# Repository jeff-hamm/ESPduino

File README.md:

# espduino
A platform that assists in making writing and deploying code for the ESP8266 as easy as writing arduino code.

#External Dependencies
Eagle 7.2
Python27
SimpleParse 2.1
GerbV http://sourceforge.net/projects/gerbv/files/gerbv/gerbv-2.6.0/gerbvinst-2.6.0.exe

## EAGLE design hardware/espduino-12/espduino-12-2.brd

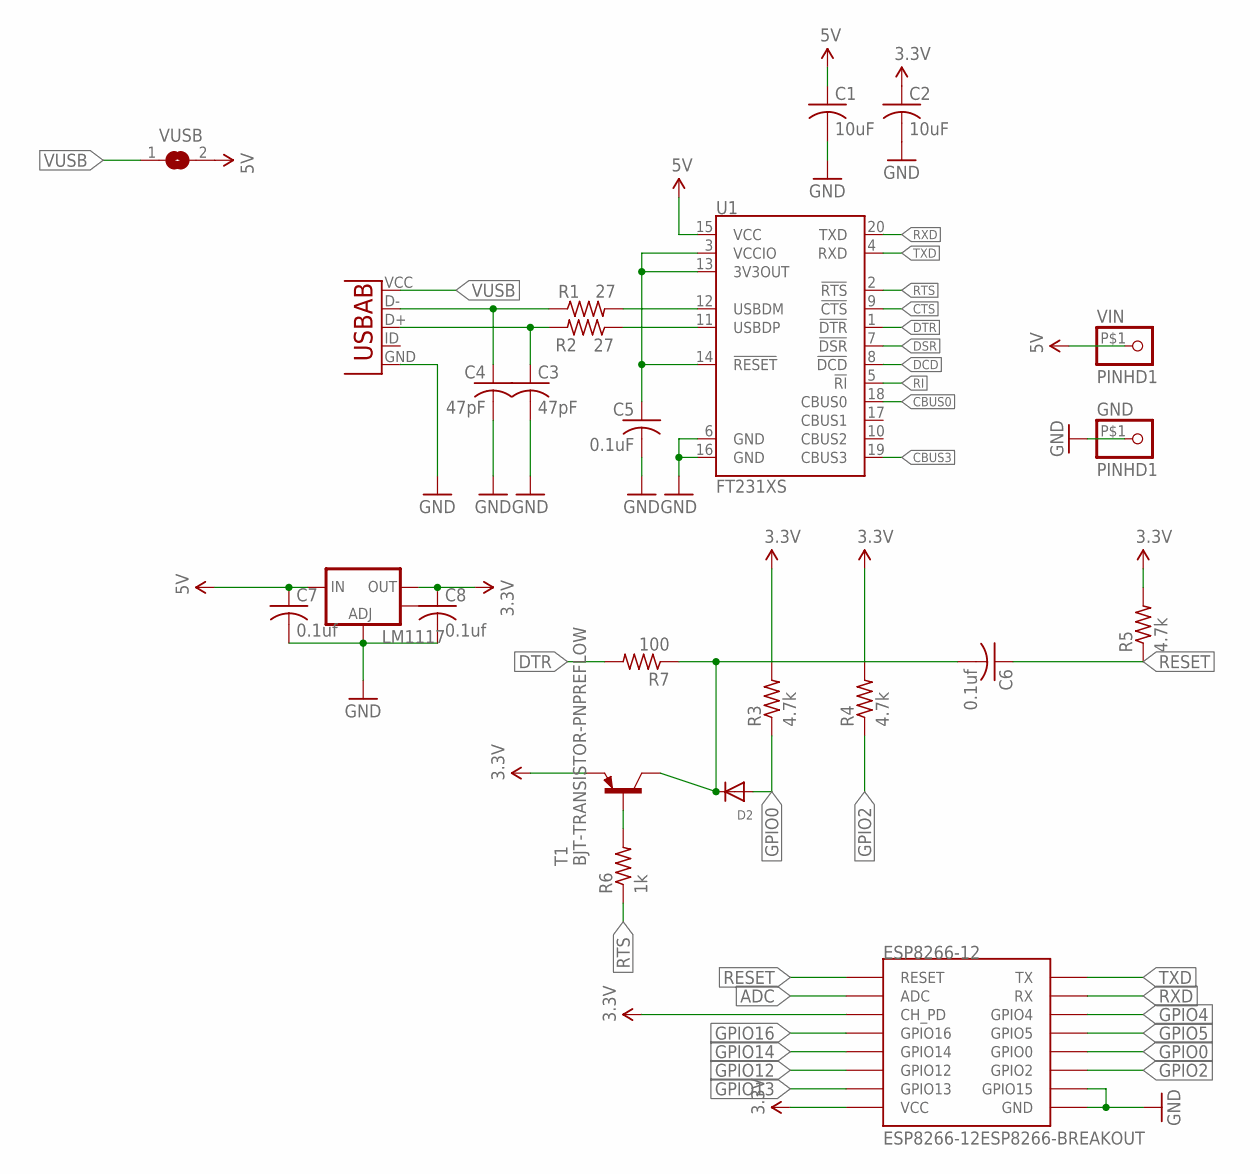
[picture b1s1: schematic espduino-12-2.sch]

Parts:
C1, C2: 10uF; C0603
C3, C4: 47pF; C0603
C5: 0.1uF; C0603
C6, C7, C8: 0.1uf; C0603
D2: DIODESOT23_REFLOW; SOT23-R
ESP8266-12: ESP8266-12ESP8266-BREAKOUT; ESP8266-12-EXT-HEADERS
GND: PINHD1
LM1117: V_REG_LM1117SOT223; SOT223
R1, R2: 27; R0603
R3, R4, R5: 4.7k; R0603
R6: 1k; R0603
R7: 100; R0603
T1: BJT-TRANSISTOR-PNPREFLOW; SOT23-R
U1: FT231XS; SSOP20_L
U2: USB-AB; MICRO-USB-A01SB141B1
VIN: PINHD1
VUSB: SJCUTTABLE; SJ-CUTTABLE

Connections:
3.3V: C2.1, C8.1, ESP8266-12.CH_PD, ESP8266-12.VCC, ESP8266-12.VCC_P (VCC), LM1117.2 (OUT), R3.2, R4.2, R5.2, T1.2 (E)
5V: C1.1, C7.1, LM1117.3 (IN), U1.15 (VCC), VIN.P$1, VUSB.2
ADC: ESP8266-12.ADC, ESP8266-12.ADC_P (ADC)
CBUS0: U1.18 (CBUS0)
CBUS3: U1.19 (CBUS3)
CTS: U1.9 (!CTS)
DCD: U1.8 (!DCD)
DSR: U1.7 (!DSR)
DTR: R7.2, U1.1 (!DTR)
GND: C1.2, C2.2, C3.2, C4.2, C5.2, C7.2, C8.2, ESP8266-12.GND, ESP8266-12.GND_P (GND), ESP8266-12.GPIO15, GND.P$1, LM1117.1 (ADJ), U1.6 (GND), U1.16 (GND), U2.GND
GPIO0: D2.1 (A), ESP8266-12.GPIO0, ESP8266-12.GPIO0_P (GPIO0), R3.1
GPIO2: ESP8266-12.GPIO2, ESP8266-12.GPIO2_P (GPIO2), R4.1
GPIO4: ESP8266-12.GPIO4, ESP8266-12.GPIO4_P (GPIO4)
GPIO5: ESP8266-12.GPIO5, ESP8266-12.GPIO5_P (GPIO5)
GPIO12: ESP8266-12.GPIO12, ESP8266-12.GPIO12_P (GPIO12)
GPIO13: ESP8266-12.GPIO13, ESP8266-12.GPIO13_P (GPIO13)
GPIO14: ESP8266-12.GPIO14, ESP8266-12.GPIO14_P (GPIO14)
GPIO16: ESP8266-12.GPIO16, ESP8266-12.GPIO_16_P (GPIO16)
unnamed: R1.2, U1.12 (USBDM)
unnamed: R2.1, U1.11 (USBDP)
unnamed: C3.1, R2.2, U2.D+
unnamed: C4.1, R1.1, U2.D-
unnamed: C5.1, U1.3 (VCCIO), U1.13 (3V3OUT), U1.14 (!RESET)
unnamed: R6.2, T1.1 (B)
NOT_DTR: C6.2, D2.3 (C), R7.1, T1.3 (C)
RESET: C6.1, ESP8266-12.RESET, ESP8266-12.RST_P (RESET), R5.1
RI: U1.5 (!RI)
RTS: R6.1, U1.2 (!RTS)
RXD: ESP8266-12.RX, ESP8266-12.RX_P (RX), U1.20 (TXD)
TXD: ESP8266-12.TX, ESP8266-12.TX_P (TX), U1.4 (RXD)
VUSB: U2.VCC (VBUS), VUSB.1

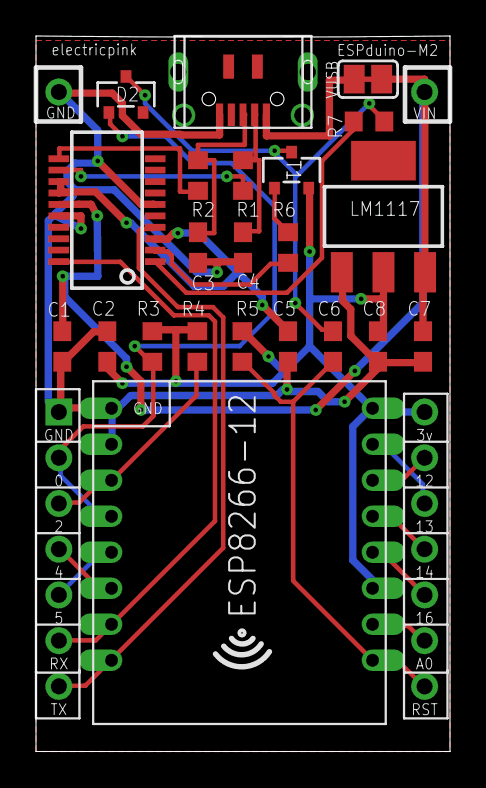
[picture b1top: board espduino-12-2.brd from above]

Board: 2 copper layers, 23.0 x 39.8 mm, 25 parts (0 on the bottom side), 25 nets.

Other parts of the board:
U$2: JUMPER-LOGO-X-SMALL

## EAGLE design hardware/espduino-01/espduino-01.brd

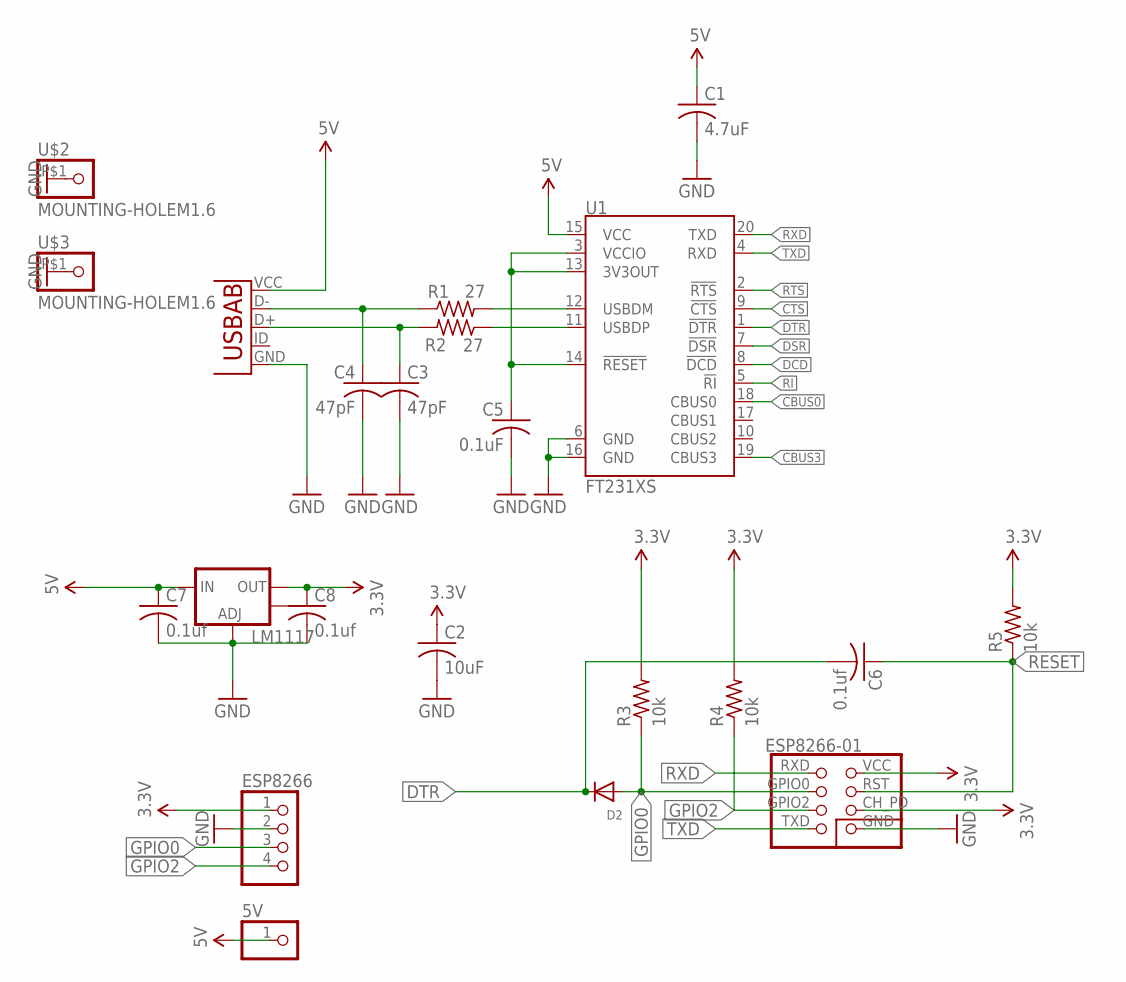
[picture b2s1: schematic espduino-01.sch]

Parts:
5V: PINHD-1X1; 1X01
C1: 4.7uF; C0603
C2: 10uF; C0603
C3, C4: 47pF; C0603
C5: 0.1uF; C0603
C6, C7, C8: 0.1uf; C0603
D2: DIODESOT23_REFLOW; SOT23-R
ESP8266: PINHD-1X4; 1X04
ESP8266-01: ESP8266ESP8266-01-MIN; ESP8266-01-MIN
LM1117: V_REG_LM1117SOT223; SOT223
R1, R2: 27; R0603
R3, R4, R5: 10k; R0603
U1: FT231XS; SSOP20_L
U2: USB-AB; MICRO-USB-A01SB141B1
U$2, U$3: MOUNTING-HOLEM1.6; M1_6MOUNTING_HOLE

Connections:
3.3V: C2.1, C8.1, ESP8266.1, ESP8266-01.CH_PD, ESP8266-01.VCC, LM1117.2 (OUT), R3.2, R4.2, R5.2
5V: 5V.1, C1.1, C7.1, LM1117.3 (IN), U1.15 (VCC), U2.VCC (VBUS)
CBUS0: U1.18 (CBUS0)
CBUS3: U1.19 (CBUS3)
CTS: U1.9 (!CTS)
DCD: U1.8 (!DCD)
DSR: U1.7 (!DSR)
DTR: C6.2, D2.3 (C), U1.1 (!DTR)
GND: C1.2, C2.2, C3.2, C4.2, C5.2, C7.2, C8.2, ESP8266.2, ESP8266-01.GND, LM1117.1 (ADJ), U1.6 (GND), U1.16 (GND), U2.GND, U$2.P$1, U$3.P$1
GPIO0: D2.1 (A), ESP8266.3, ESP8266-01.GPIO0, R3.1
GPIO2: ESP8266.4, ESP8266-01.GPIO2, R4.1
unnamed: R1.2, U1.12 (USBDM)
unnamed: R2.1, U1.11 (USBDP)
unnamed: C3.1, R2.2, U2.D+
unnamed: C4.1, R1.1, U2.D-
unnamed: C5.1, U1.3 (VCCIO), U1.13 (3V3OUT), U1.14 (!RESET)
RESET: C6.1, ESP8266-01.RST, R5.1
RI: U1.5 (!RI)
RTS: U1.2 (!RTS)
RXD: ESP8266-01.RXD, U1.20 (TXD)
TXD: ESP8266-01.TXD, U1.4 (RXD)

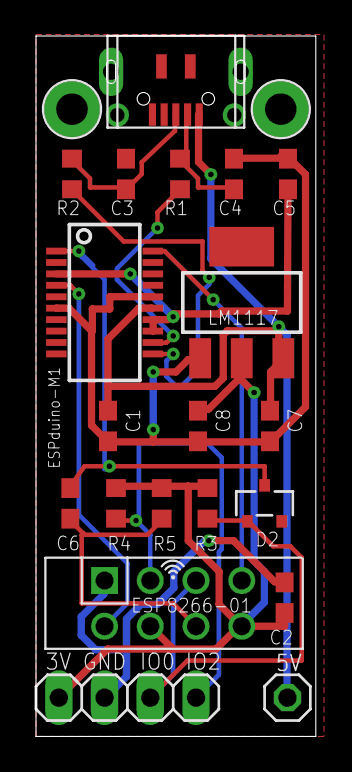
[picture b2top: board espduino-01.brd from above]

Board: 2 copper layers, 15.5 x 38.9 mm, 23 parts (0 on the bottom side), 14 nets.

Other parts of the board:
U$1: JUMPER-LOGO-X-SMALL

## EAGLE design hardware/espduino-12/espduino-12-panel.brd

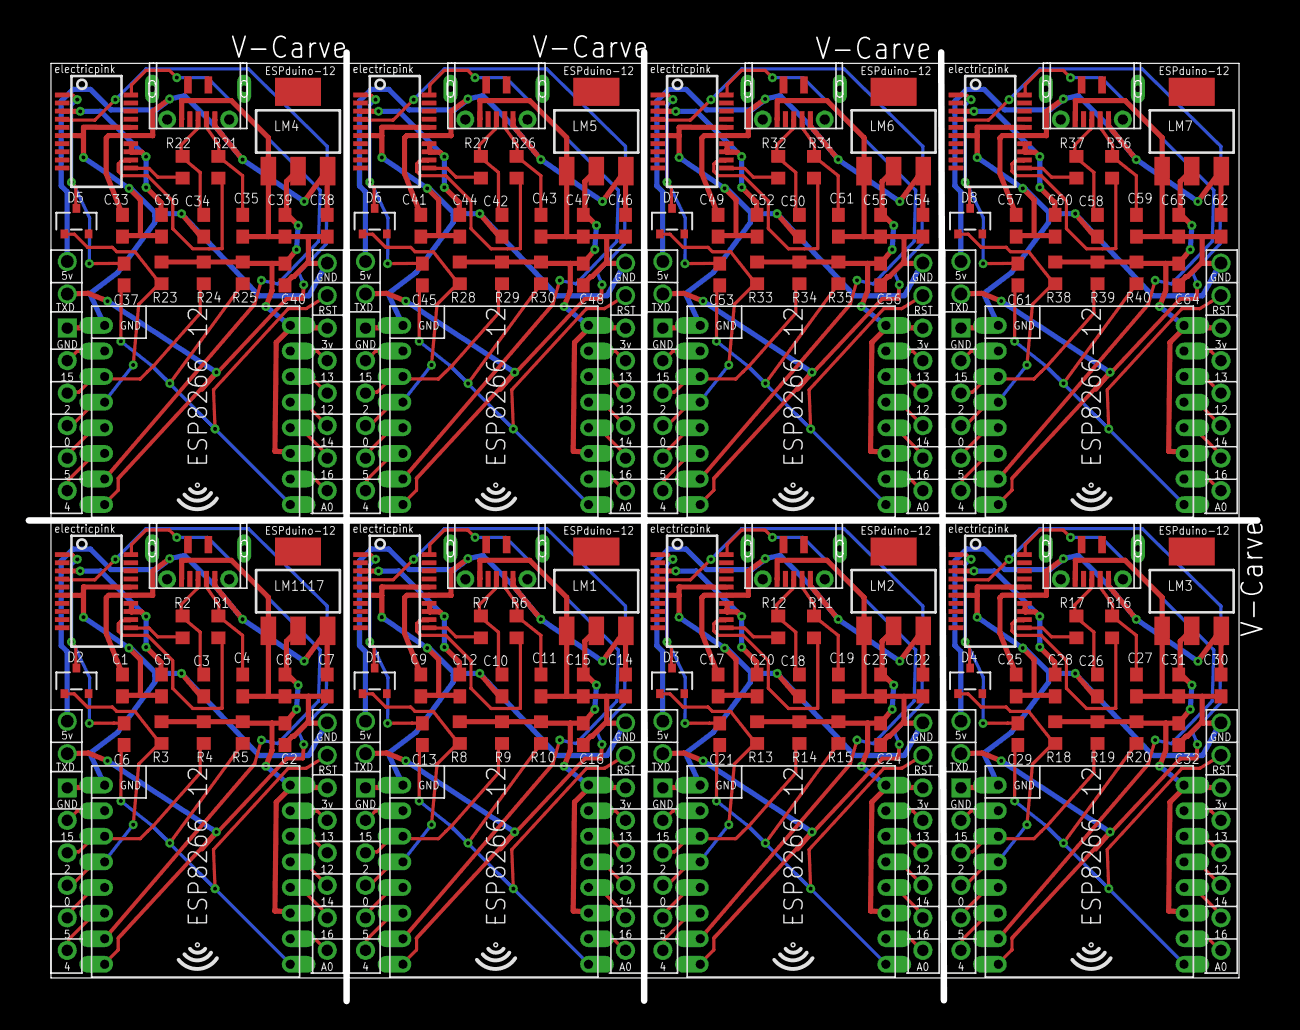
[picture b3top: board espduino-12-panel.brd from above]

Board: 2 copper layers, 97.1 x 76.0 mm, 152 parts (0 on the bottom side), 176 nets.

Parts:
C1, C9, C17, C25, C33, C41, C49, C57: 4.7uF; C0603
C2, C16, C24, C32, C40, C48, C56, C64: 10uF; C0603
C3, C4, C10, C11, C18, C19, C26, C27, C34, C35, C42, C43, C50, C51, C58, C59: 47pF; C0603
C5, C12, C20, C28, C36, C44, C52, C60: 0.1uF; C0603
C6, C7, C8, C13, C14, C15, C21, C22, C23, C29, C30, C31, C37, C38, C39, C45, C46, C47, C53, C54, C55, C61, C62, C63: 0.1uf; C0603
D1, D2, D3, D4, D5, D6, D7, D8: SOT23-R
ESP8266-1, ESP8266-2, ESP8266-3, ESP8266-4, ESP8266-5, ESP8266-6, ESP8266-7, ESP8266-12: ESP8266-12ESP8266-BREAKOUT; ESP8266-12-EXT-HEADERS
LM1, LM2, LM3, LM4, LM5, LM6, LM7, LM1117: SOT223
R1, R2, R6, R7, R11, R12, R16, R17, R21, R22, R26, R27, R31, R32, R36, R37: 27; R0603
R3, R4, R5, R8, R9, R10, R13, R14, R15, R18, R19, R20, R23, R24, R25, R28, R29, R30, R33, R34, R35, R38, R39, R40: 10k; R0603
U1, U3, U5, U7, U9, U11, U13, U15: FT231XS; SSOP20_L
U2, U4, U6, U8, U10, U12, U14, U16: MICRO-USB-A01SB141B1
U$1, U$2, U$3, U$4, U$5, U$6, U$7, U$8: JUMPER-LOGO-X-SMALL

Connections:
3.3V: C2.1, C8.1, ESP8266-12.CH_PD, ESP8266-12.VCC, ESP8266-12.VCC_P, LM1117.2, R3.2, R4.2, R5.2
3.3V1: C15.1, C16.1, ESP8266-1.CH_PD, ESP8266-1.VCC, ESP8266-1.VCC_P, LM1.2, R8.2, R9.2, R10.2
3.3V2: C23.1, C24.1, ESP8266-2.CH_PD, ESP8266-2.VCC, ESP8266-2.VCC_P, LM2.2, R13.2, R14.2, R15.2
3.3V3: C31.1, C32.1, ESP8266-3.CH_PD, ESP8266-3.VCC, ESP8266-3.VCC_P, LM3.2, R18.2, R19.2, R20.2
3.3V4: C39.1, C40.1, ESP8266-4.CH_PD, ESP8266-4.VCC, ESP8266-4.VCC_P, LM4.2, R23.2, R24.2, R25.2
3.3V5: C47.1, C48.1, ESP8266-5.CH_PD, ESP8266-5.VCC, ESP8266-5.VCC_P, LM5.2, R28.2, R29.2, R30.2
3.3V6: C55.1, C56.1, ESP8266-6.CH_PD, ESP8266-6.VCC, ESP8266-6.VCC_P, LM6.2, R33.2, R34.2, R35.2
3.3V7: C63.1, C64.1, ESP8266-7.CH_PD, ESP8266-7.VCC, ESP8266-7.VCC_P, LM7.2, R38.2, R39.2, R40.2
5V: C1.1, C7.1, LM1117.3, U1.15, U2.VCC
5V1: C9.1, C14.1, LM1.3, U3.15, U4.VCC
5V2: C17.1, C22.1, LM2.3, U5.15, U6.VCC
5V3: C25.1, C30.1, LM3.3, U7.15, U8.VCC
5V4: C33.1, C38.1, LM4.3, U9.15, U10.VCC
5V5: C41.1, C46.1, LM5.3, U11.15, U12.VCC
5V6: C49.1, C54.1, LM6.3, U13.15, U14.VCC
5V7: C57.1, C62.1, LM7.3, U15.15, U16.VCC
ADC: ESP8266-12.ADC, ESP8266-12.ADC_P
ADC1: ESP8266-1.ADC, ESP8266-1.ADC_P
ADC2: ESP8266-2.ADC, ESP8266-2.ADC_P
ADC3: ESP8266-3.ADC, ESP8266-3.ADC_P
ADC4: ESP8266-4.ADC, ESP8266-4.ADC_P
ADC5: ESP8266-5.ADC, ESP8266-5.ADC_P
ADC6: ESP8266-6.ADC, ESP8266-6.ADC_P
ADC7: ESP8266-7.ADC, ESP8266-7.ADC_P
DTR: C6.2, D2.3, U1.1
DTR1: C13.2, D1.3, U3.1
DTR2: C21.2, D3.3, U5.1
DTR3: C29.2, D4.3, U7.1
DTR4: C37.2, D5.3, U9.1
DTR5: C45.2, D6.3, U11.1
DTR6: C53.2, D7.3, U13.1
DTR7: C61.2, D8.3, U15.1
GND: C1.2, C2.2, C3.2, C4.2, C5.2, C7.2, C8.2, ESP8266-12.GND, ESP8266-12.GND_P, LM1117.1, U1.6, U1.16, U2.GND
GND1: C9.2, C10.2, C11.2, C12.2, C14.2, C15.2, C16.2, ESP8266-1.GND, ESP8266-1.GND_P, LM1.1, U3.6, U3.16, U4.GND
GND2: C17.2, C18.2, C19.2, C20.2, C22.2, C23.2, C24.2, ESP8266-2.GND, ESP8266-2.GND_P, LM2.1, U5.6, U5.16, U6.GND
GND3: C25.2, C26.2, C27.2, C28.2, C30.2, C31.2, C32.2, ESP8266-3.GND, ESP8266-3.GND_P, LM3.1, U7.6, U7.16, U8.GND
GND4: C33.2, C34.2, C35.2, C36.2, C38.2, C39.2, C40.2, ESP8266-4.GND, ESP8266-4.GND_P, LM4.1, U9.6, U9.16, U10.GND
GND5: C41.2, C42.2, C43.2, C44.2, C46.2, C47.2, C48.2, ESP8266-5.GND, ESP8266-5.GND_P, LM5.1, U11.6, U11.16, U12.GND
GND6: C49.2, C50.2, C51.2, C52.2, C54.2, C55.2, C56.2, ESP8266-6.GND, ESP8266-6.GND_P, LM6.1, U13.6, U13.16, U14.GND
GND7: C57.2, C58.2, C59.2, C60.2, C62.2, C63.2, C64.2, ESP8266-7.GND, ESP8266-7.GND_P, LM7.1, U15.6, U15.16, U16.GND
GPIO0: D2.1, ESP8266-12.GPIO0, ESP8266-12.GPIO0_P, R3.1
GPIO1: D1.1, ESP8266-1.GPIO0, ESP8266-1.GPIO0_P, R8.1
GPIO2: ESP8266-12.GPIO2, ESP8266-12.GPIO2_P, R4.1
GPIO3: ESP8266-1.GPIO2, ESP8266-1.GPIO2_P, R9.1
GPIO4: ESP8266-12.GPIO4, ESP8266-12.GPIO4_P
GPIO5: ESP8266-12.GPIO5, ESP8266-12.GPIO5_P
GPIO6: ESP8266-1.GPIO16, ESP8266-1.GPIO_16_P
GPIO7: ESP8266-1.GPIO14, ESP8266-1.GPIO14_P
GPIO8: ESP8266-1.GPIO12, ESP8266-1.GPIO12_P
GPIO9: ESP8266-1.GPIO13, ESP8266-1.GPIO13_P
GPIO10: ESP8266-1.GPIO4, ESP8266-1.GPIO4_P
GPIO11: ESP8266-1.GPIO5, ESP8266-1.GPIO5_P
GPIO12: ESP8266-12.GPIO12, ESP8266-12.GPIO12_P
GPIO13: ESP8266-12.GPIO13, ESP8266-12.GPIO13_P
GPIO14: ESP8266-12.GPIO14, ESP8266-12.GPIO14_P
GPIO15: ESP8266-12.GPIO15, ESP8266-12.GPIO15_P
GPIO16: ESP8266-12.GPIO16, ESP8266-12.GPIO_16_P
GPIO17: ESP8266-1.GPIO15, ESP8266-1.GPIO15_P
GPIO18: D3.1, ESP8266-2.GPIO0, ESP8266-2.GPIO0_P, R13.1
GPIO19: ESP8266-2.GPIO2, ESP8266-2.GPIO2_P, R14.1
GPIO20: ESP8266-2.GPIO16, ESP8266-2.GPIO_16_P
GPIO21: ESP8266-2.GPIO14, ESP8266-2.GPIO14_P
GPIO22: ESP8266-2.GPIO12, ESP8266-2.GPIO12_P
GPIO23: ESP8266-2.GPIO13, ESP8266-2.GPIO13_P
GPIO24: ESP8266-2.GPIO4, ESP8266-2.GPIO4_P
GPIO25: ESP8266-2.GPIO5, ESP8266-2.GPIO5_P
GPIO26: ESP8266-2.GPIO15, ESP8266-2.GPIO15_P
GPIO27: D4.1, ESP8266-3.GPIO0, ESP8266-3.GPIO0_P, R18.1
GPIO28: ESP8266-3.GPIO2, ESP8266-3.GPIO2_P, R19.1
GPIO29: ESP8266-3.GPIO16, ESP8266-3.GPIO_16_P
GPIO30: ESP8266-3.GPIO14, ESP8266-3.GPIO14_P
GPIO31: ESP8266-3.GPIO12, ESP8266-3.GPIO12_P
GPIO32: ESP8266-3.GPIO13, ESP8266-3.GPIO13_P
GPIO33: ESP8266-3.GPIO4, ESP8266-3.GPIO4_P
GPIO34: ESP8266-3.GPIO5, ESP8266-3.GPIO5_P
GPIO35: ESP8266-3.GPIO15, ESP8266-3.GPIO15_P
GPIO36: D5.1, ESP8266-4.GPIO0, ESP8266-4.GPIO0_P, R23.1
GPIO37: ESP8266-4.GPIO2, ESP8266-4.GPIO2_P, R24.1
GPIO38: ESP8266-4.GPIO16, ESP8266-4.GPIO_16_P
GPIO39: ESP8266-4.GPIO14, ESP8266-4.GPIO14_P
GPIO40: ESP8266-4.GPIO12, ESP8266-4.GPIO12_P
GPIO41: ESP8266-4.GPIO13, ESP8266-4.GPIO13_P
GPIO42: ESP8266-4.GPIO4, ESP8266-4.GPIO4_P
GPIO43: ESP8266-4.GPIO5, ESP8266-4.GPIO5_P
GPIO44: ESP8266-4.GPIO15, ESP8266-4.GPIO15_P
GPIO45: D6.1, ESP8266-5.GPIO0, ESP8266-5.GPIO0_P, R28.1
GPIO46: ESP8266-5.GPIO2, ESP8266-5.GPIO2_P, R29.1
GPIO47: ESP8266-5.GPIO16, ESP8266-5.GPIO_16_P
GPIO48: ESP8266-5.GPIO14, ESP8266-5.GPIO14_P
GPIO49: ESP8266-5.GPIO12, ESP8266-5.GPIO12_P
GPIO50: ESP8266-5.GPIO13, ESP8266-5.GPIO13_P
GPIO51: ESP8266-5.GPIO4, ESP8266-5.GPIO4_P
GPIO52: ESP8266-5.GPIO5, ESP8266-5.GPIO5_P
GPIO53: ESP8266-5.GPIO15, ESP8266-5.GPIO15_P
GPIO54: D7.1, ESP8266-6.GPIO0, ESP8266-6.GPIO0_P, R33.1
GPIO55: ESP8266-6.GPIO2, ESP8266-6.GPIO2_P, R34.1
GPIO56: ESP8266-6.GPIO16, ESP8266-6.GPIO_16_P
GPIO57: ESP8266-6.GPIO14, ESP8266-6.GPIO14_P
GPIO58: ESP8266-6.GPIO12, ESP8266-6.GPIO12_P
GPIO59: ESP8266-6.GPIO13, ESP8266-6.GPIO13_P
GPIO60: ESP8266-6.GPIO4, ESP8266-6.GPIO4_P
GPIO61: ESP8266-6.GPIO5, ESP8266-6.GPIO5_P
GPIO62: ESP8266-6.GPIO15, ESP8266-6.GPIO15_P
GPIO63: D8.1, ESP8266-7.GPIO0, ESP8266-7.GPIO0_P, R38.1
GPIO64: ESP8266-7.GPIO2, ESP8266-7.GPIO2_P, R39.1
GPIO65: ESP8266-7.GPIO16, ESP8266-7.GPIO_16_P
GPIO66: ESP8266-7.GPIO14, ESP8266-7.GPIO14_P
GPIO67: ESP8266-7.GPIO12, ESP8266-7.GPIO12_P
GPIO68: ESP8266-7.GPIO13, ESP8266-7.GPIO13_P
GPIO69: ESP8266-7.GPIO4, ESP8266-7.GPIO4_P
GPIO70: ESP8266-7.GPIO5, ESP8266-7.GPIO5_P
GPIO71: ESP8266-7.GPIO15, ESP8266-7.GPIO15_P
unnamed: R1.2, U1.12
unnamed: R2.1, U1.11
unnamed: C3.1, R2.2, U2.D+
unnamed: C4.1, R1.1, U2.D-
unnamed: C5.1, U1.3, U1.13, U1.14
unnamed: R6.2, U3.12
unnamed: R7.1, U3.11
unnamed: C10.1, R7.2, U4.D+
unnamed: C11.1, R6.1, U4.D-
unnamed: C12.1, U3.3, U3.13, U3.14
unnamed: R11.2, U5.12
unnamed: R12.1, U5.11
unnamed: C18.1, R12.2, U6.D+
unnamed: C19.1, R11.1, U6.D-
unnamed: C20.1, U5.3, U5.13, U5.14
unnamed: R16.2, U7.12
unnamed: R17.1, U7.11
unnamed: C26.1, R17.2, U8.D+
unnamed: C27.1, R16.1, U8.D-
unnamed: C28.1, U7.3, U7.13, U7.14
unnamed: R21.2, U9.12
unnamed: R22.1, U9.11
unnamed: C34.1, R22.2, U10.D+
unnamed: C35.1, R21.1, U10.D-
unnamed: C36.1, U9.3, U9.13, U9.14
unnamed: R26.2, U11.12
unnamed: R27.1, U11.11
unnamed: C42.1, R27.2, U12.D+
unnamed: C43.1, R26.1, U12.D-
unnamed: C44.1, U11.3, U11.13, U11.14
unnamed: R31.2, U13.12
unnamed: R32.1, U13.11
unnamed: C50.1, R32.2, U14.D+
unnamed: C51.1, R31.1, U14.D-
unnamed: C52.1, U13.3, U13.13, U13.14
unnamed: R36.2, U15.12
unnamed: R37.1, U15.11
unnamed: C58.1, R37.2, U16.D+
unnamed: C59.1, R36.1, U16.D-
unnamed: C60.1, U15.3, U15.13, U15.14
RESET: C6.1, ESP8266-12.RESET, R5.1
RESET1: C13.1, ESP8266-1.RESET, R10.1
RESET2: C21.1, ESP8266-2.RESET, R15.1
RESET3: C29.1, ESP8266-3.RESET, R20.1
RESET4: C37.1, ESP8266-4.RESET, R25.1
RESET5: C45.1, ESP8266-5.RESET, R30.1
RESET6: C53.1, ESP8266-6.RESET, R35.1
RESET7: C61.1, ESP8266-7.RESET, R40.1
RXD: ESP8266-12.RX, U1.20
RXD1: ESP8266-1.RX, U3.20
RXD2: ESP8266-2.RX, U5.20
RXD3: ESP8266-3.RX, U7.20
RXD4: ESP8266-4.RX, U9.20
RXD5: ESP8266-5.RX, U11.20
RXD6: ESP8266-6.RX, U13.20
RXD7: ESP8266-7.RX, U15.20
TXD: ESP8266-12.TX, U1.4
TXD1: ESP8266-1.TX, U3.4
TXD2: ESP8266-2.TX, U5.4
TXD3: ESP8266-3.TX, U7.4
TXD4: ESP8266-4.TX, U9.4
TXD5: ESP8266-5.TX, U11.4
TXD6: ESP8266-6.TX, U13.4
TXD7: ESP8266-7.TX, U15.4

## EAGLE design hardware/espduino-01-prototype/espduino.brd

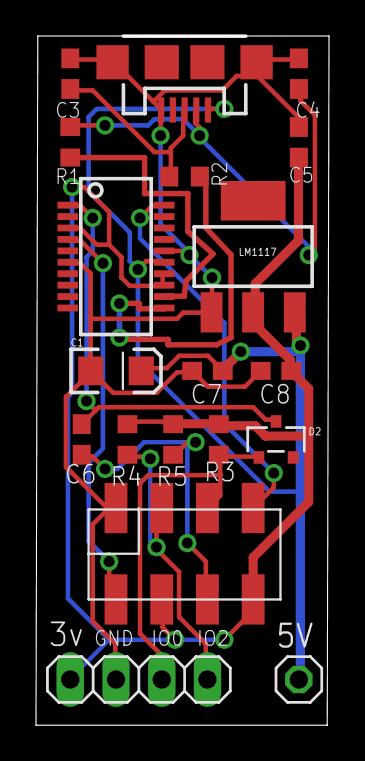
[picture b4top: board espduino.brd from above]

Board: 2 copper layers, 16.3 x 38.3 mm, 20 parts (0 on the bottom side), 13 nets.

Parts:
5V: 1X01
C1: 10uF; EIA3216
C3, C4: 47pF; C0603
C5: 0.1uF; C0603
C6, C7, C8: 0.1uf; C0603
D2: SOT23-R
ESP8266: 1X04
LM1117: SOT223
R1, R2: 27; R0603
R3, R4: 100k; R0603
R5: 10k; R0603
U1: FT231XS; SSOP20_L
U$1: ESP8266HEADERS; ESP8266-01-HD
U$2: JUMPER-LOGO
X1: USB-MICROB

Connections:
3.3V: C5.1, C8.1, ESP8266.1, LM1117.2, R3.2, R4.2, R5.2, U1.3, U1.13, U1.14, U$1.CH_PD, U$1.VCC
5V: 5V.1, C1.A, C7.1, LM1117.3, U1.15, X1.VBUS
DTR: C6.2, D2.3, U1.1
GND: C1.C, C3.2, C4.2, C5.2, C7.2, C8.2, ESP8266.2, LM1117.1, U1.6, U1.16, U$1.GND, X1.GND, X1.MT1, X1.MT2
GPIO0: D2.1, ESP8266.3, R3.1, U$1.GPIO0
GPIO2: ESP8266.4, R4.1, U$1.GPIO2
unnamed: R1.2, U1.12
unnamed: R2.1, U1.11
unnamed: C3.1, R2.2, X1.D+
unnamed: C4.1, R1.1, X1.D-
RESET: C6.1, R5.1, U$1.RST
RXD: U1.20, U$1.RXD
TXD: U1.4, U$1.TXD

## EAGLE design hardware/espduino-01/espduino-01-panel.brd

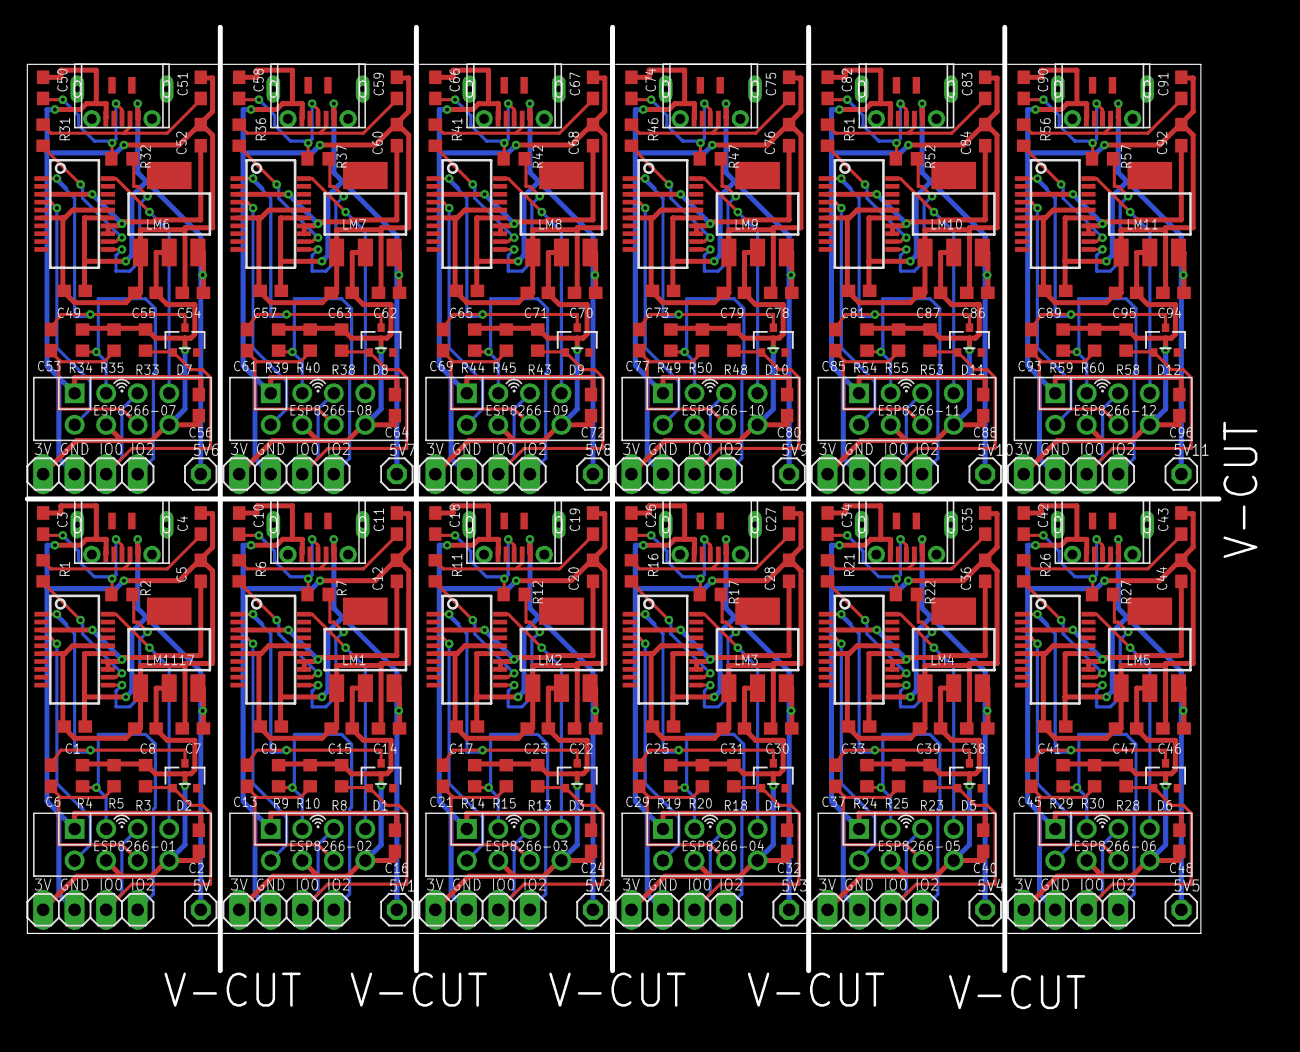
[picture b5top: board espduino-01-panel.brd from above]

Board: 2 copper layers, 100.3 x 80.3 mm, 252 parts (0 on the bottom side), 168 nets.

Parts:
5V, 5V1, 5V2, 5V3, 5V4, 5V5, 5V6, 5V7, 5V8, 5V9, 5V10, 5V11: 1X01
C1, C9, C17, C25, C33, C41, C49, C57, C65, C73, C81, C89: 4.7uF; C0603
C2, C16, C24, C32, C40, C48, C56, C64, C72, C80, C88, C96: 10uF; C0603
C3, C4, C10, C11, C18, C19, C26, C27, C34, C35, C42, C43, C50, C51, C58, C59, C66, C67, C74, C75, C82, C83, C90, C91: 47pF; C0603
C5, C12, C20, C28, C36, C44, C52, C60, C68, C76, C84, C92: 0.1uF; C0603
C6, C7, C8, C13, C14, C15, C21, C22, C23, C29, C30, C31, C37, C38, C39, C45, C46, C47, C53, C54, C55, C61, C62, C63, C69, C70, C71, C77, C78, C79, C85, C86, C87, C93, C94, C95: 0.1uf; C0603
D1, D2, D3, D4, D5, D6, D7, D8, D9, D10, D11, D12: SOT23-R
ESP1, ESP2, ESP3, ESP4, ESP5, ESP6, ESP7, ESP8, ESP9, ESP10, ESP11, ESP8266: 1X04
ESP8266-01, ESP8266-02, ESP8266-03, ESP8266-04, ESP8266-05, ESP8266-06, ESP8266-07, ESP8266-08, ESP8266-09, ESP8266-10, ESP8266-11, ESP8266-12: ESP8266ESP8266-01-MIN; ESP8266-01-MIN
LM1, LM2, LM3, LM4, LM5, LM6, LM7, LM8, LM9, LM10, LM11, LM1117: SOT223
R1, R2, R6, R7, R11, R12, R16, R17, R21, R22, R26, R27, R31, R32, R36, R37, R41, R42, R46, R47, R51, R52, R56, R57: 27; R0603
R3, R4, R5, R8, R9, R10, R13, R14, R15, R18, R19, R20, R23, R24, R25, R28, R29, R30, R33, R34, R35, R38, R39, R40, R43, R44, R45, R48, R49, R50, R53, R54, R55, R58, R59, R60: 10k; R0603
U1, U3, U5, U7, U9, U11, U13, U15, U17, U19, U21, U23: FT231XS; SSOP20_L
U2, U4, U6, U8, U10, U12, U14, U16, U18, U20, U22, U24: MICRO-USB-A01SB141B1
U$1, U$2, U$3, U$4, U$5, U$6, U$7, U$8, U$9, U$10, U$11, U$12: JUMPER-LOGO-X-SMALL

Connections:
3.3V: C2.1, C8.1, ESP8266.1, ESP8266-01.CH_PD, ESP8266-01.VCC, LM1117.2, R3.2, R4.2, R5.2
3.3V1: C15.1, C16.1, ESP1.1, ESP8266-02.CH_PD, ESP8266-02.VCC, LM1.2, R8.2, R9.2, R10.2
3.3V2: C23.1, C24.1, ESP2.1, ESP8266-03.CH_PD, ESP8266-03.VCC, LM2.2, R13.2, R14.2, R15.2
3.3V3: C31.1, C32.1, ESP3.1, ESP8266-04.CH_PD, ESP8266-04.VCC, LM3.2, R18.2, R19.2, R20.2
3.3V4: C39.1, C40.1, ESP4.1, ESP8266-05.CH_PD, ESP8266-05.VCC, LM4.2, R23.2, R24.2, R25.2
3.3V5: C47.1, C48.1, ESP5.1, ESP8266-06.CH_PD, ESP8266-06.VCC, LM5.2, R28.2, R29.2, R30.2
3.3V6: C55.1, C56.1, ESP6.1, ESP8266-07.CH_PD, ESP8266-07.VCC, LM6.2, R33.2, R34.2, R35.2
3.3V7: C63.1, C64.1, ESP7.1, ESP8266-08.CH_PD, ESP8266-08.VCC, LM7.2, R38.2, R39.2, R40.2
3.3V8: C71.1, C72.1, ESP8.1, ESP8266-09.CH_PD, ESP8266-09.VCC, LM8.2, R43.2, R44.2, R45.2
3.3V9: C79.1, C80.1, ESP9.1, ESP8266-10.CH_PD, ESP8266-10.VCC, LM9.2, R48.2, R49.2, R50.2
3.3V10: C87.1, C88.1, ESP10.1, ESP8266-11.CH_PD, ESP8266-11.VCC, LM10.2, R53.2, R54.2, R55.2
3.3V11: C95.1, C96.1, ESP11.1, ESP8266-12.CH_PD, ESP8266-12.VCC, LM11.2, R58.2, R59.2, R60.2
5V: 5V.1, C1.1, C7.1, LM1117.3, U1.15, U2.VCC
5V1: 5V1.1, C9.1, C14.1, LM1.3, U3.15, U4.VCC
5V2: 5V2.1, C17.1, C22.1, LM2.3, U5.15, U6.VCC
5V3: 5V3.1, C25.1, C30.1, LM3.3, U7.15, U8.VCC
5V4: 5V4.1, C33.1, C38.1, LM4.3, U9.15, U10.VCC
5V5: 5V5.1, C41.1, C46.1, LM5.3, U11.15, U12.VCC
5V6: 5V6.1, C49.1, C54.1, LM6.3, U13.15, U14.VCC
5V7: 5V7.1, C57.1, C62.1, LM7.3, U15.15, U16.VCC
5V8: 5V8.1, C65.1, C70.1, LM8.3, U17.15, U18.VCC
5V9: 5V9.1, C73.1, C78.1, LM9.3, U19.15, U20.VCC
5V10: 5V10.1, C81.1, C86.1, LM10.3, U21.15, U22.VCC
5V11: 5V11.1, C89.1, C94.1, LM11.3, U23.15, U24.VCC
DTR: C6.2, D2.3, U1.1
DTR1: C13.2, D1.3, U3.1
DTR2: C21.2, D3.3, U5.1
DTR3: C29.2, D4.3, U7.1
DTR4: C37.2, D5.3, U9.1
DTR5: C45.2, D6.3, U11.1
DTR6: C53.2, D7.3, U13.1
DTR7: C61.2, D8.3, U15.1
DTR8: C69.2, D9.3, U17.1
DTR9: C77.2, D10.3, U19.1
DTR10: C85.2, D11.3, U21.1
DTR11: C93.2, D12.3, U23.1
GND: C1.2, C2.2, C3.2, C4.2, C5.2, C7.2, C8.2, ESP8266.2, ESP8266-01.GND, LM1117.1, U1.6, U1.16, U2.GND
GND1: C9.2, C10.2, C11.2, C12.2, C14.2, C15.2, C16.2, ESP1.2, ESP8266-02.GND, LM1.1, U3.6, U3.16, U4.GND
GND2: C17.2, C18.2, C19.2, C20.2, C22.2, C23.2, C24.2, ESP2.2, ESP8266-03.GND, LM2.1, U5.6, U5.16, U6.GND
GND3: C25.2, C26.2, C27.2, C28.2, C30.2, C31.2, C32.2, ESP3.2, ESP8266-04.GND, LM3.1, U7.6, U7.16, U8.GND
GND4: C33.2, C34.2, C35.2, C36.2, C38.2, C39.2, C40.2, ESP4.2, ESP8266-05.GND, LM4.1, U9.6, U9.16, U10.GND
GND5: C41.2, C42.2, C43.2, C44.2, C46.2, C47.2, C48.2, ESP5.2, ESP8266-06.GND, LM5.1, U11.6, U11.16, U12.GND
GND6: C49.2, C50.2, C51.2, C52.2, C54.2, C55.2, C56.2, ESP6.2, ESP8266-07.GND, LM6.1, U13.6, U13.16, U14.GND
GND7: C57.2, C58.2, C59.2, C60.2, C62.2, C63.2, C64.2, ESP7.2, ESP8266-08.GND, LM7.1, U15.6, U15.16, U16.GND
GND8: C65.2, C66.2, C67.2, C68.2, C70.2, C71.2, C72.2, ESP8.2, ESP8266-09.GND, LM8.1, U17.6, U17.16, U18.GND
GND9: C73.2, C74.2, C75.2, C76.2, C78.2, C79.2, C80.2, ESP9.2, ESP8266-10.GND, LM9.1, U19.6, U19.16, U20.GND
GND10: C81.2, C82.2, C83.2, C84.2, C86.2, C87.2, C88.2, ESP10.2, ESP8266-11.GND, LM10.1, U21.6, U21.16, U22.GND
GND11: C89.2, C90.2, C91.2, C92.2, C94.2, C95.2, C96.2, ESP11.2, ESP8266-12.GND, LM11.1, U23.6, U23.16, U24.GND
GPIO0: D2.1, ESP8266.3, ESP8266-01.GPIO0, R3.1
GPIO1: D1.1, ESP1.3, ESP8266-02.GPIO0, R8.1
GPIO2: ESP8266.4, ESP8266-01.GPIO2, R4.1
GPIO3: ESP1.4, ESP8266-02.GPIO2, R9.1
GPIO4: D3.1, ESP2.3, ESP8266-03.GPIO0, R13.1
GPIO5: ESP2.4, ESP8266-03.GPIO2, R14.1
GPIO6: D4.1, ESP3.3, ESP8266-04.GPIO0, R18.1
GPIO7: ESP3.4, ESP8266-04.GPIO2, R19.1
GPIO8: D5.1, ESP4.3, ESP8266-05.GPIO0, R23.1
GPIO9: ESP4.4, ESP8266-05.GPIO2, R24.1
GPIO10: D6.1, ESP5.3, ESP8266-06.GPIO0, R28.1
GPIO11: ESP5.4, ESP8266-06.GPIO2, R29.1
GPIO12: D7.1, ESP6.3, ESP8266-07.GPIO0, R33.1
GPIO13: ESP6.4, ESP8266-07.GPIO2, R34.1
GPIO14: D8.1, ESP7.3, ESP8266-08.GPIO0, R38.1
GPIO15: ESP7.4, ESP8266-08.GPIO2, R39.1
GPIO16: D9.1, ESP8.3, ESP8266-09.GPIO0, R43.1
GPIO17: ESP8.4, ESP8266-09.GPIO2, R44.1
GPIO18: D10.1, ESP9.3, ESP8266-10.GPIO0, R48.1
GPIO19: ESP9.4, ESP8266-10.GPIO2, R49.1
GPIO20: D11.1, ESP10.3, ESP8266-11.GPIO0, R53.1
GPIO21: ESP10.4, ESP8266-11.GPIO2, R54.1
GPIO22: D12.1, ESP11.3, ESP8266-12.GPIO0, R58.1
GPIO23: ESP11.4, ESP8266-12.GPIO2, R59.1
unnamed: R1.2, U1.12
unnamed: R2.1, U1.11
unnamed: C3.1, R2.2, U2.D+
unnamed: C4.1, R1.1, U2.D-
unnamed: C5.1, U1.3, U1.13, U1.14
unnamed: R6.2, U3.12
unnamed: R7.1, U3.11
unnamed: C10.1, R7.2, U4.D+
unnamed: C11.1, R6.1, U4.D-
unnamed: C12.1, U3.3, U3.13, U3.14
unnamed: R11.2, U5.12
unnamed: R12.1, U5.11
unnamed: C18.1, R12.2, U6.D+
unnamed: C19.1, R11.1, U6.D-
unnamed: C20.1, U5.3, U5.13, U5.14
unnamed: R16.2, U7.12
unnamed: R17.1, U7.11
unnamed: C26.1, R17.2, U8.D+
unnamed: C27.1, R16.1, U8.D-
unnamed: C28.1, U7.3, U7.13, U7.14
unnamed: R21.2, U9.12
unnamed: R22.1, U9.11
unnamed: C34.1, R22.2, U10.D+
unnamed: C35.1, R21.1, U10.D-
unnamed: C36.1, U9.3, U9.13, U9.14
unnamed: R26.2, U11.12
unnamed: R27.1, U11.11
unnamed: C42.1, R27.2, U12.D+
unnamed: C43.1, R26.1, U12.D-
unnamed: C44.1, U11.3, U11.13, U11.14
unnamed: R31.2, U13.12
unnamed: R32.1, U13.11
unnamed: C50.1, R32.2, U14.D+
unnamed: C51.1, R31.1, U14.D-
unnamed: C52.1, U13.3, U13.13, U13.14
unnamed: R36.2, U15.12
unnamed: R37.1, U15.11
unnamed: C58.1, R37.2, U16.D+
unnamed: C59.1, R36.1, U16.D-
unnamed: C60.1, U15.3, U15.13, U15.14
unnamed: R41.2, U17.12
unnamed: R42.1, U17.11
unnamed: C66.1, R42.2, U18.D+
unnamed: C67.1, R41.1, U18.D-
unnamed: C68.1, U17.3, U17.13, U17.14
unnamed: R46.2, U19.12
unnamed: R47.1, U19.11
unnamed: C74.1, R47.2, U20.D+
unnamed: C75.1, R46.1, U20.D-
unnamed: C76.1, U19.3, U19.13, U19.14
unnamed: R51.2, U21.12
unnamed: R52.1, U21.11
unnamed: C82.1, R52.2, U22.D+
unnamed: C83.1, R51.1, U22.D-
unnamed: C84.1, U21.3, U21.13, U21.14
unnamed: R56.2, U23.12
unnamed: R57.1, U23.11
unnamed: C90.1, R57.2, U24.D+
unnamed: C91.1, R56.1, U24.D-
unnamed: C92.1, U23.3, U23.13, U23.14
RESET: C6.1, ESP8266-01.RST, R5.1
RESET1: C13.1, ESP8266-02.RST, R10.1
RESET2: C21.1, ESP8266-03.RST, R15.1
RESET3: C29.1, ESP8266-04.RST, R20.1
RESET4: C37.1, ESP8266-05.RST, R25.1
RESET5: C45.1, ESP8266-06.RST, R30.1
RESET6: C53.1, ESP8266-07.RST, R35.1
RESET7: C61.1, ESP8266-08.RST, R40.1
RESET8: C69.1, ESP8266-09.RST, R45.1
RESET9: C77.1, ESP8266-10.RST, R50.1
RESET10: C85.1, ESP8266-11.RST, R55.1
RESET11: C93.1, ESP8266-12.RST, R60.1
RXD: ESP8266-01.RXD, U1.20
RXD1: ESP8266-02.RXD, U3.20
RXD2: ESP8266-03.RXD, U5.20
RXD3: ESP8266-04.RXD, U7.20
RXD4: ESP8266-05.RXD, U9.20
RXD5: ESP8266-06.RXD, U11.20
RXD6: ESP8266-07.RXD, U13.20
RXD7: ESP8266-08.RXD, U15.20
RXD8: ESP8266-09.RXD, U17.20
RXD9: ESP8266-10.RXD, U19.20
RXD10: ESP8266-11.RXD, U21.20
RXD11: ESP8266-12.RXD, U23.20
TXD: ESP8266-01.TXD, U1.4
TXD1: ESP8266-02.TXD, U3.4
TXD2: ESP8266-03.TXD, U5.4
TXD3: ESP8266-04.TXD, U7.4
TXD4: ESP8266-05.TXD, U9.4
TXD5: ESP8266-06.TXD, U11.4
TXD6: ESP8266-07.TXD, U13.4
TXD7: ESP8266-08.TXD, U15.4
TXD8: ESP8266-09.TXD, U17.4
TXD9: ESP8266-10.TXD, U19.4
TXD10: ESP8266-11.TXD, U21.4
TXD11: ESP8266-12.TXD, U23.4

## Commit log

2015-04-21 Initial ESP-01 Commit
2015-04-21 ESPduino-01 sent for manufacture
2015-04-21 ESPduino-12-v1 Sent to manufacturer
2015-05-26 Rev 2 of espduino-m2

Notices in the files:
parts and their libraries:
SparkFun-Passives: Licensing: CC v3.0 Share-Alike You are welcome to use this library for commercial purposes.
SparkFun-PowerIC: Licensing: Creative Commons ShareAlike 4.0 International - https://creativecommons.org/licenses/by-sa/4.0
